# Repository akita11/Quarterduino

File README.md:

# Quarterduino

Half-size (Quater-area) Arduino UNO compatible

# Author

Junichi Akita (akita@ifdl.jp, @akita11)

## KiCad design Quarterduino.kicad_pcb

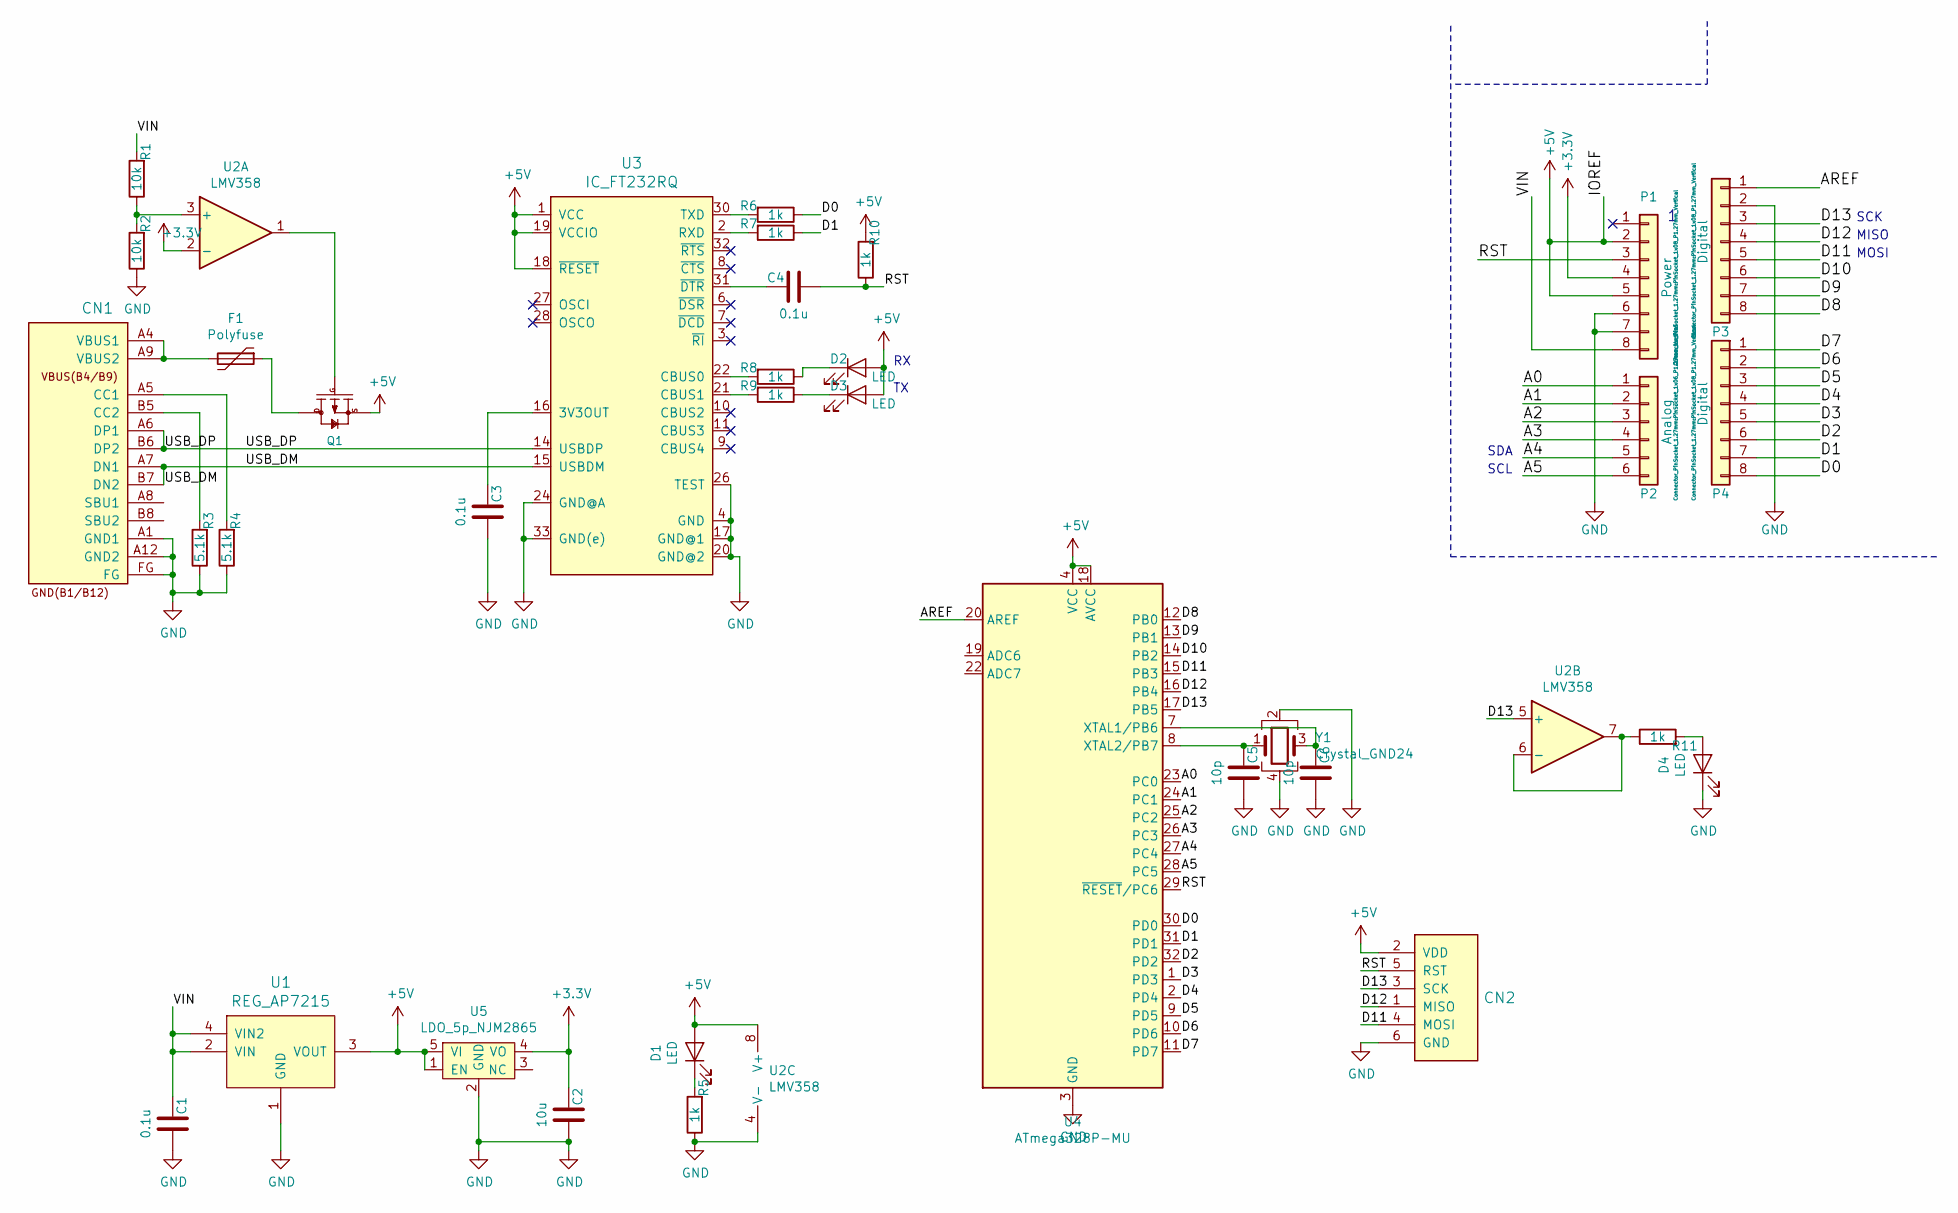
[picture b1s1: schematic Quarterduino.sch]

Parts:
C1, C3, C4: 0.1u; C_0603_1608Metric
C2: 10u; C_0603_1608Metric
C5, C6: 10p; C_0603_1608Metric
CN1: CON_USB-C-16; USB-C_16P_TH
CN2: CON_AVRISP; PinHeader_2x03_P1.27mm_Vertical
D1, D2, D3, D4: LED; LED_0603_1608Metric
F1: Polyfuse; R_1210_3225Metric
P1: Power; PinSocket_1x08_P1.27mm_Vertical
P2: Analog; PinSocket_1x06_P1.27mm_Vertical
P3, P4: Digital; PinSocket_1x08_P1.27mm_Vertical
Q1: FDN340P; SOT-23; MPN FDN340P
R1, R2: 10k; R_0603_1608Metric
R3, R4: 5.1k; R_0603_1608Metric
R5, R6, R7, R8, R9, R10, R11: 1k; R_0603_1608Metric
U1: REG_AP7215; SOT89-3L_TAB
U2: LMV358; VSSOP-8_3.0x3.0mm_P0.65mm
U3: IC_FT232RQ; QFN-32-1EP_5x5mm_P0.5mm_EP3.45x3.45mm_ThermalVias
U4: ATmega328P-MU; QFN-32-1EP_5x5mm_P0.5mm_EP3.1x3.1mm
U5: LDO_5p_NJM2865; SOT-23-5
Y1: Crystal_GND24; Crystal_3.2x2.5mm_4p

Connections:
+3V3: C2.2, P1.4, U2.2 (-), U5.4 (VO)
+5V: CN2.2 (VDD), D1.2 (A), D2.2 (A), D3.2 (A), P1.2, P1.5, Q1.2 (S), R10.2, U1.3 (VOUT), U2.8 (V+), U3.1 (VCC), U3.18 (~RESET), U3.19 (VCCIO), U4.4 (VCC), U4.6 (VCC), U4.18 (AVCC), U5.1 (EN), U5.5 (VI)
/A0: P2.1, U4.23 (PC0)
/A1: P2.2, U4.24 (PC1)
/A2: P2.3, U4.25 (PC2)
/A3: P2.4, U4.26 (PC3)
/A4: P2.5, U4.27 (PC4)
/A5: P2.6, U4.28 (PC5)
/AREF: P3.1, U4.20 (AREF)
/D0: P4.8, R6.1, U4.30 (PD0)
/D1: P4.7, R7.1, U4.31 (PD1)
/D2: P4.6, U4.32 (PD2)
/D3: P4.5, U4.1 (PD3)
/D4: P4.4, U4.2 (PD4)
/D5: P4.3, U4.9 (PD5)
/D6: P4.2, U4.10 (PD6)
/D7: P4.1, U4.11 (PD7)
/D8: P3.8, U4.12 (PB0)
/D9: P3.7, U4.13 (PB1)
/D10: P3.6, U4.14 (PB2)
/D11: CN2.4 (MOSI), P3.5, U4.15 (PB3)
/D12: CN2.1 (MISO), P3.4, U4.16 (PB4)
/D13: CN2.3 (SCK), P3.3, U2.5 (+), U4.17 (PB5)
/RST: C4.1, CN2.5 (RST), P1.3, R10.1, U4.29 (~RESET~/PC6)
/USB_DM: CN1.A7 (DN1), CN1.B7 (DN2), U3.15 (USBDM)
/USB_DP: CN1.A6 (DP1), CN1.B6 (DP2), U3.14 (USBDP)
/VIN: C1.2, P1.8, R1.2, U1.2 (VIN), U1.4 (VIN2)
GND: C1.1, C2.1, C3.1, C5.1, C6.1, CN1.A1 (GND1), CN1.A12 (GND2), CN1.FG, CN2.6 (GND), D4.1 (K), P1.6, P1.7, P3.2, R2.1, R3.1, R4.1, R5.1, U1.1 (GND), U2.4 (V-), U3.4 (GND), U3.17 (GND@1), U3.20 (GND@2), U3.24 (GND@A), U3.26 (TEST), U3.33 (GND(e)), U4.3 (GND), U4.5 (GND), U4.21 (GND), U4.33 (GND), U5.2 (GND), Y1.2, Y1.4
unnamed: C3.2, U3.16 (3V3OUT)
unnamed: C4.2, U3.31 (~DTR)
unnamed: C5.2, U4.8 (XTAL2/PB7), Y1.1
unnamed: C6.2, U4.7 (XTAL1/PB6), Y1.3
unnamed: CN1.A4 (VBUS1), CN1.A9 (VBUS2), F1.2
unnamed: CN1.A5 (CC1), R4.2
unnamed: CN1.B5 (CC2), R3.2
unnamed: D1.1 (K), R5.2
unnamed: D2.1 (K), R8.1
unnamed: D3.1 (K), R9.1
unnamed: D4.2 (A), R11.2
unnamed: F1.1, Q1.3 (D)
unnamed: Q1.1 (G), U2.1
unnamed: R1.1, R2.2, U2.3 (+)
unnamed: R6.2, U3.30 (TXD)
unnamed: R7.2, U3.2 (RXD)
unnamed: R8.2, U3.22 (CBUS0)
unnamed: R9.2, U3.21 (CBUS1)
unnamed: R11.1, U2.6 (-), U2.7

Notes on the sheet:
SDA
SCL
SCK
MISO
MOSI

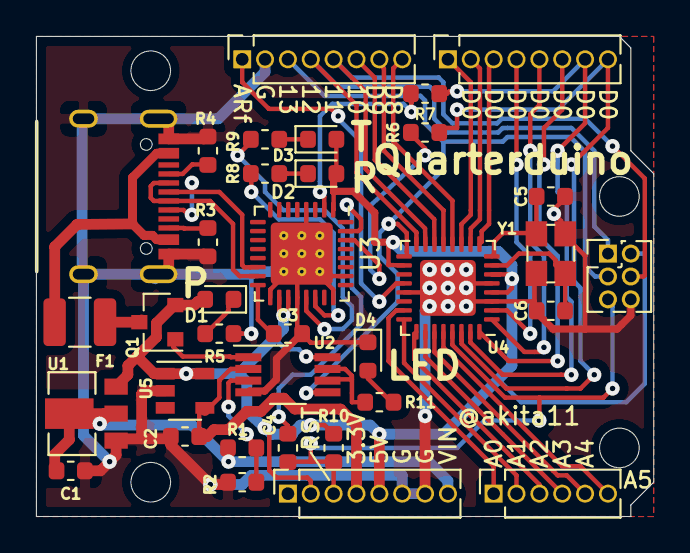
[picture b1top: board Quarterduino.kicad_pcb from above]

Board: 2 copper layers, 34.3 x 26.7 mm, 35 parts (0 on the bottom side), 47 nets.

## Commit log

2020-05-22 ファイルの追加
2020-05-22 ベタGNDの追加
